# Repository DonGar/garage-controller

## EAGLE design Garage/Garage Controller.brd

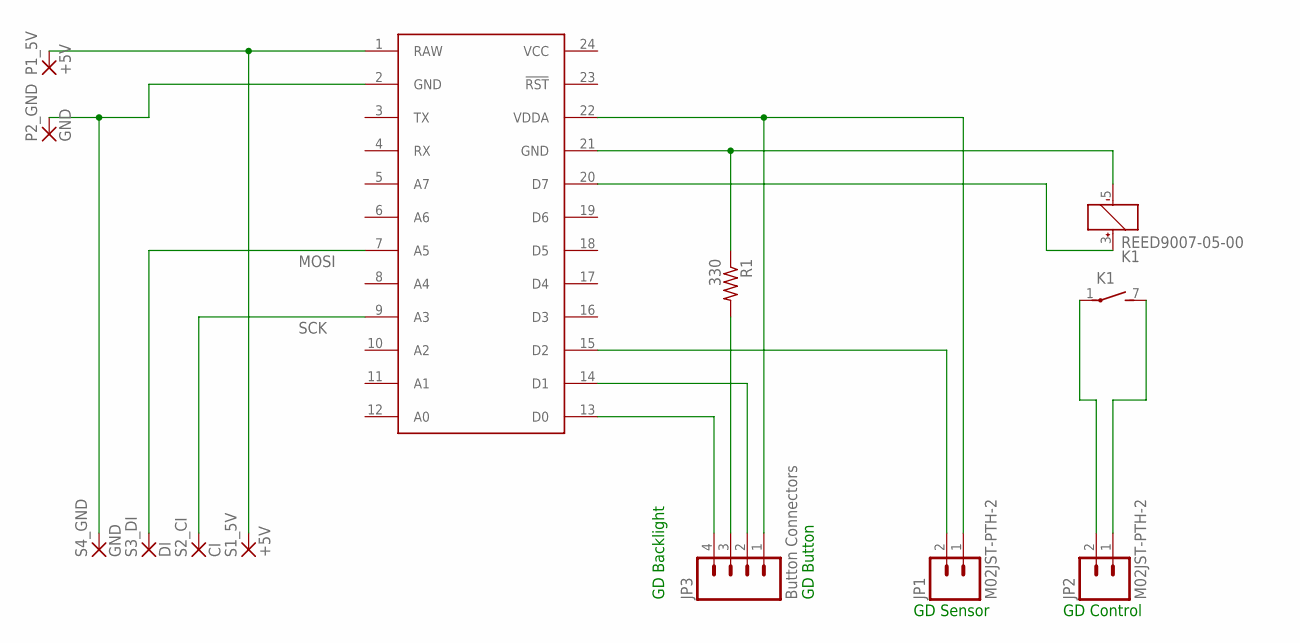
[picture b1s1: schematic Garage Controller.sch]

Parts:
CORE: SPARK_CORECORE; SPARK_CORE
JP1, JP2: M02JST-PTH-2; JST-2-PTH
JP3: Button Connectors; JST-4-PTH
K1: REED9007-05-00; REED
P1_5V: +5V; 1,6/0,8
P2_GND: GND; 1,6/0,8
R1: 330; 0207/5V
S1_5V: +5V; 1,6/0,8
S2_CI: CI; 1,6/0,8
S3_DI: DI; 1,6/0,8
S4_GND: GND; 1,6/0,8

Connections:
MOSI: CORE.7 (A5), S3_DI.1
unnamed: JP3.3, R1.2
unnamed: CORE.13 (D0), JP3.4
unnamed: CORE.21 (GND), K1.5 (-), R1.1
unnamed: CORE.22 (VDDA), JP1.1, JP3.1
unnamed: JP2.1, K1.7 (S)
unnamed: JP2.2, K1.1
unnamed: CORE.20 (D7), K1.3 (+)
unnamed: CORE.14 (D1), JP3.2
unnamed: CORE.2 (GND), P2_GND.1, S4_GND.1
unnamed: CORE.1 (RAW), P1_5V.1, S1_5V.1
unnamed: CORE.15 (D2), JP1.2
SCK: CORE.9 (A3), S2_CI.1
VCC: CORE.24 (VCC)

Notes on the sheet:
GD Sensor
GD Control
GD Backlight
GD Button

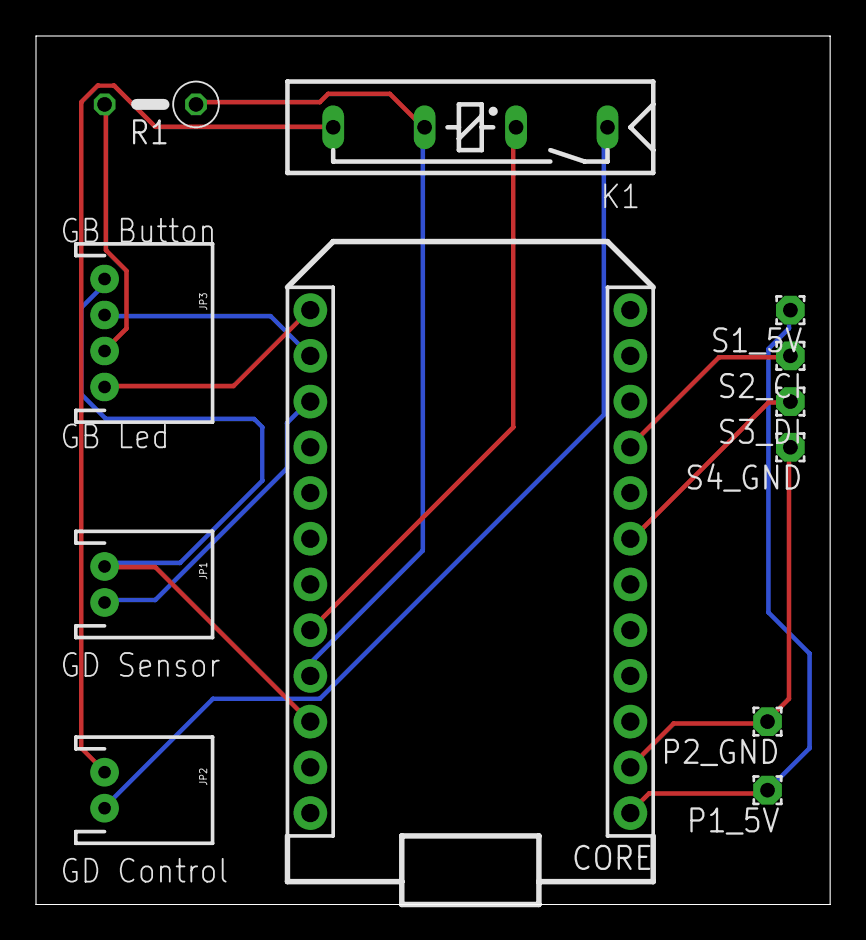
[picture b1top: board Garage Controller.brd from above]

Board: 2 copper layers, 44.1 x 48.2 mm, 12 parts (0 on the bottom side), 13 nets.

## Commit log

2015-02-25 Initial project checkin.
2015-04-11 Significant update.
2015-04-11 Require minimum button push time to activate.
    I was seeing the garage door spontaniously open from random power
    drops/spikes. Logs showed that the controller thought it's button was
    pushed. In an attempt to fix this, only count the garage door button
    as pushed if it's held down for at least 50ms.
    Also, some method renaming/reorganizing.
2015-04-12 Add a Makefile for Spark.io.
2015-05-25 Capture multiple changes.
    Updated to use external spark-strip library for managing lights.
    Revamped published events and functions to match newer "go-house"
    project conventions.
2015-10-05 Makefile: Switch to particle command.
2015-10-06 Remove sublime project.
2015-10-06 Rearrange files, no code change.
2015-10-06 Change how "strip" is published.
2015-10-10 Prep for adding particle-strip subtree.
2015-10-10 Add particle-strip sub-tree.
2015-10-10 Makefile: Add 'update_libs' target.
2017-07-11 Updated Makefile for new 'particle' command line behavior.
2018-01-13 Moved to modern particle project format. Updated from spark-strip to particle-strip.

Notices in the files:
parts and their libraries:
SparkFun-Connectors: Licensing: Creative Commons ShareAlike 4.0 International - https://creativecommons.org/licenses/by-sa/4.0
